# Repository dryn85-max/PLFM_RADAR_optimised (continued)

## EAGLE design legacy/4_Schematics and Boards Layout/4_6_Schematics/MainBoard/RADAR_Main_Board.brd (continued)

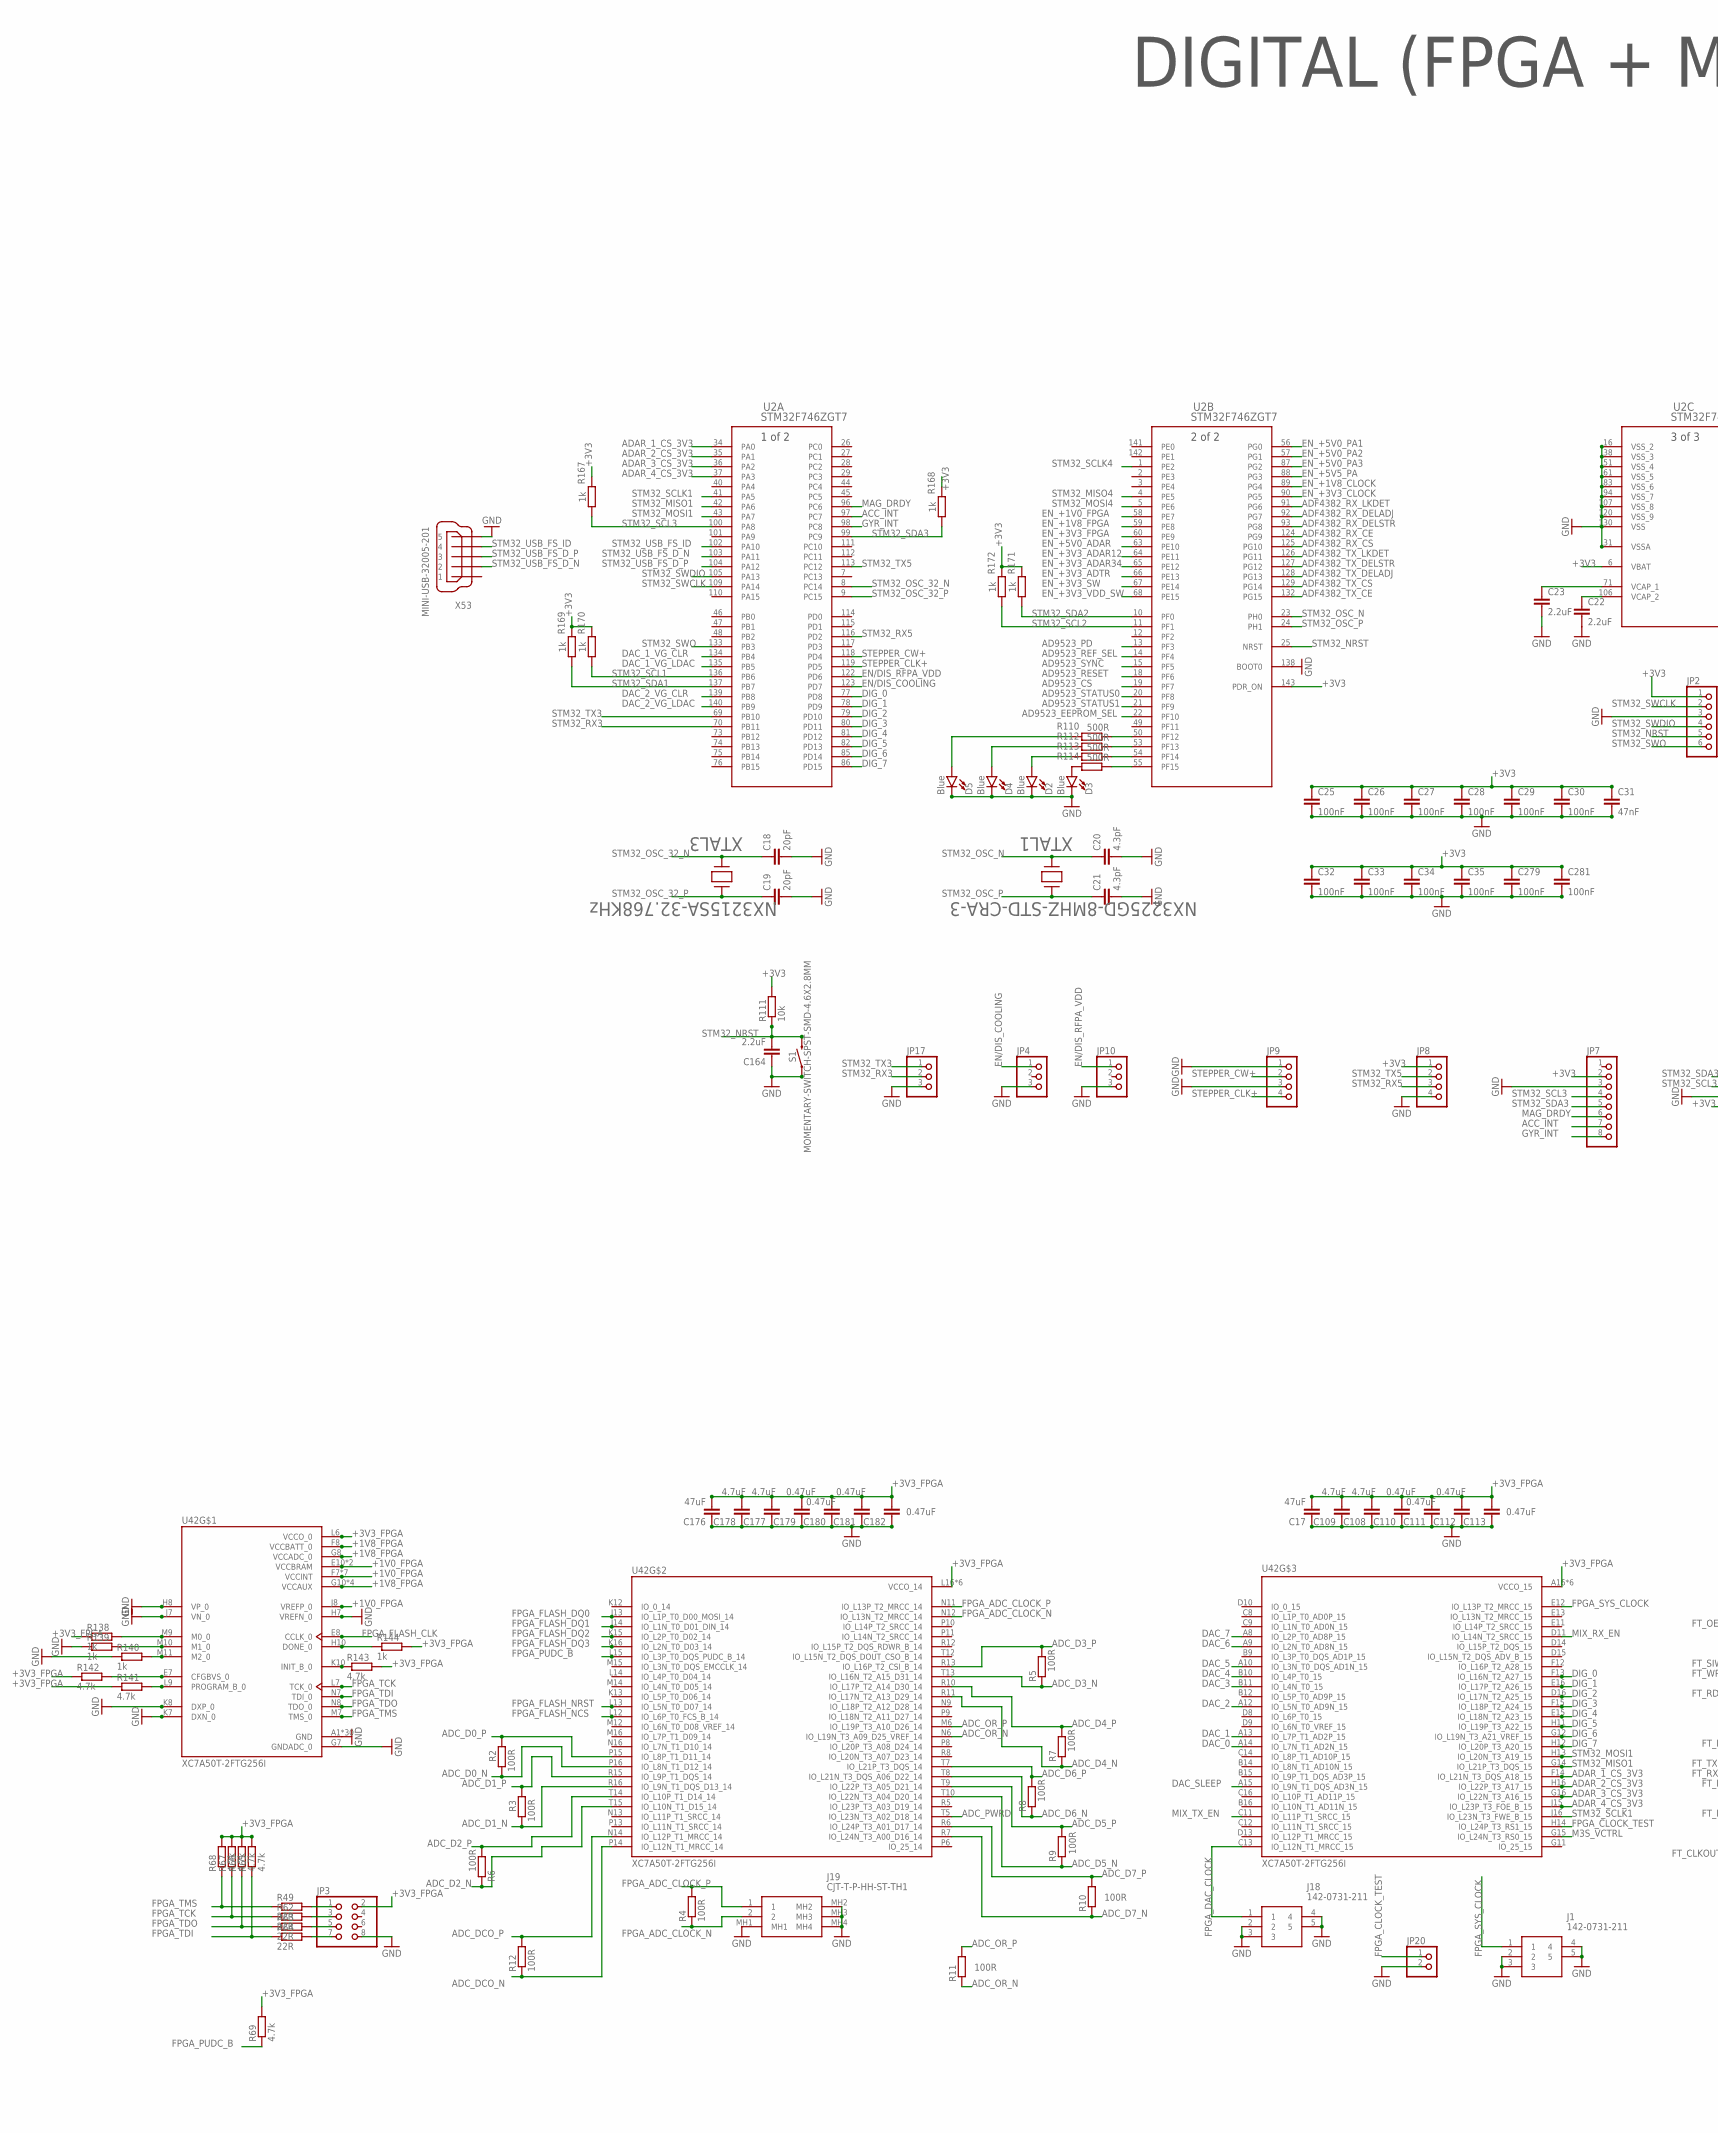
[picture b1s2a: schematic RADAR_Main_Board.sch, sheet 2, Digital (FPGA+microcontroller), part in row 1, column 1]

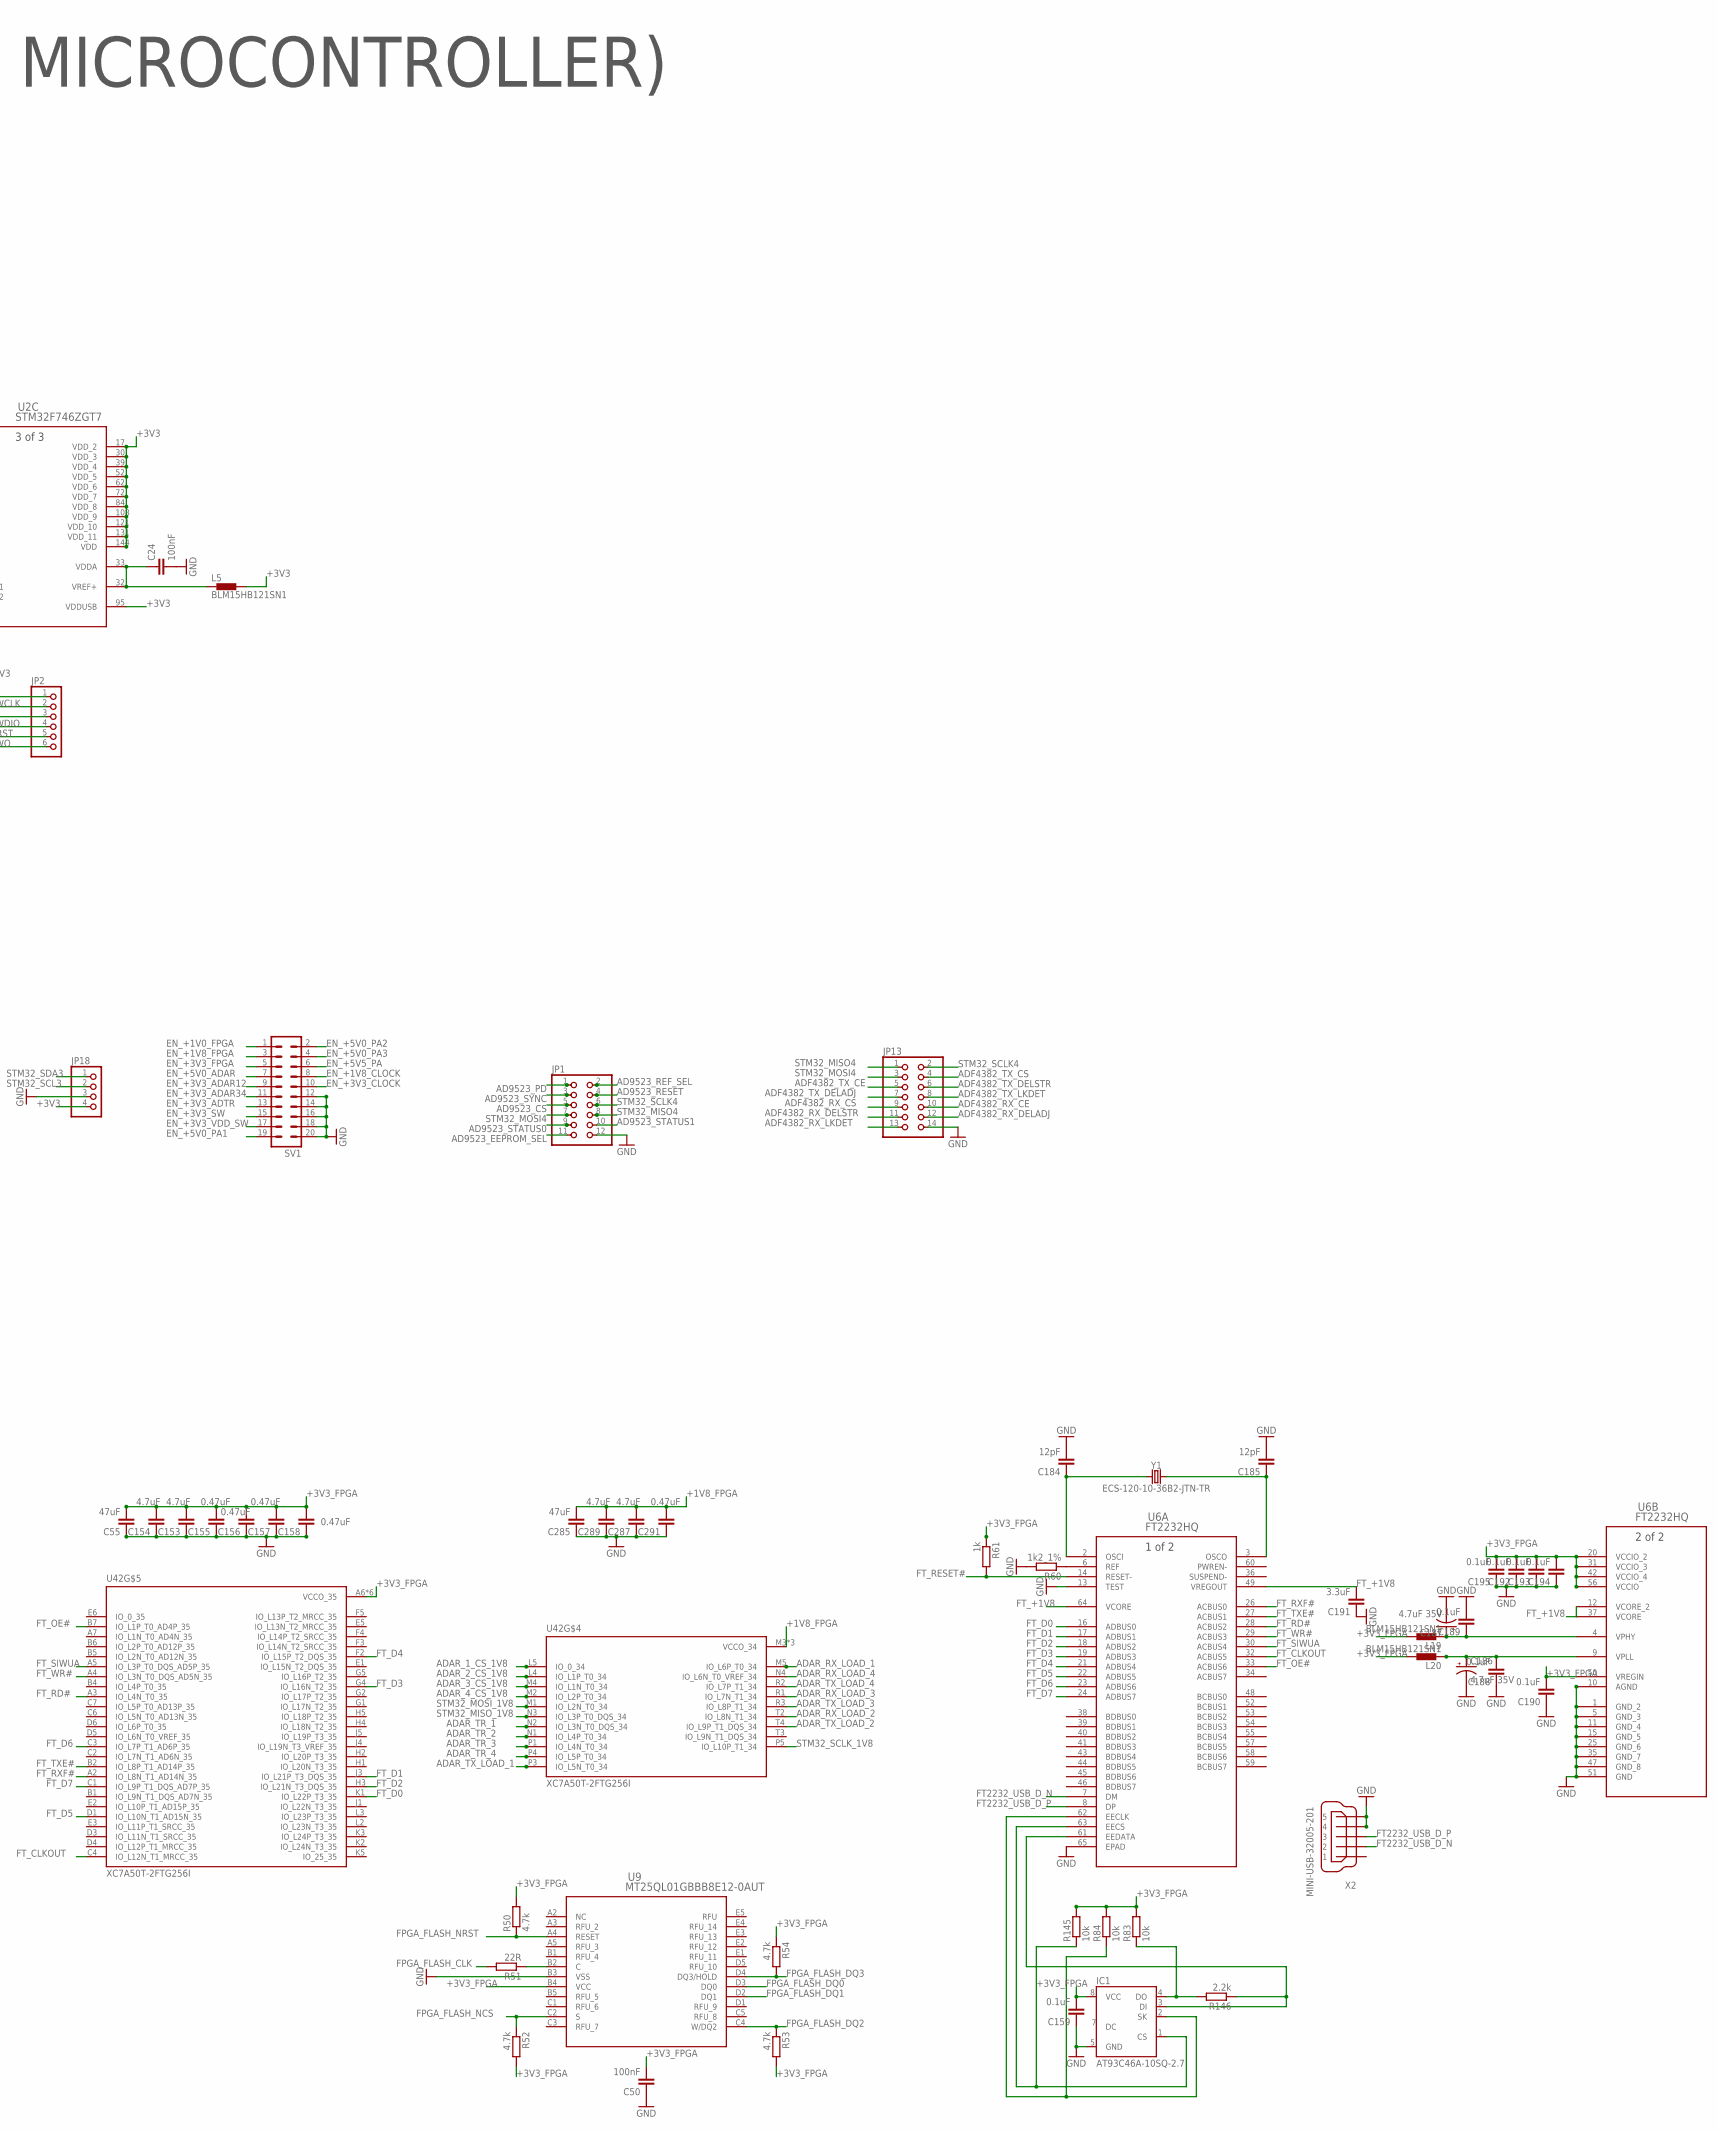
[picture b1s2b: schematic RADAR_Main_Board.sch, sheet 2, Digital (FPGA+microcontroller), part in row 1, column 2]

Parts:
C17, C55, C176, C285: 47uF; C0201
C18, C19: 20pF; C0201
C20, C21: 4.3pF; C0201
C22, C23, C164: 2.2uF; C0201
C24, C25, C26, C27, C28, C29, C30, C32, C33, C34, C35, C50, C279, C281: 100nF; C0201
C31: 47nF; C0201
C108, C109, C153, C154, C177, C178, C287, C289: 4.7uF; C0201
C110, C111, C112, C113, C155, C156, C157, C158, C179, C180, C181, C182, C291: 0.47uF; C0201
C159, C188, C189, C190, C192, C193, C194, C195: 0.1uF; C0201
C184, C185: 12pF; C0201
C186, C187: 4.7uF 35V; EIA3528
C191: 3.3uF; C0201
D2, D3, D4, D5: Blue; LED-0603
IC1: AT93C46A-10SQ-2.7; SOIC8
J1, J18: 142-0731-211; 1420731211
J19: CJT-T-P-HH-ST-TH1; CJTTPHHSTTH1
JP1: PINHD-2X6; 2X06
JP2: PINHD-1X6; 1X06
JP3: PINHD-2X4; 2X04
JP4, JP10, JP17: PINHD-1X3; 1X03
JP7: PINHD-1X8; 1X08
JP8, JP9, JP18: PINHD-1X4; 1X04
JP13: PINHD-2X7; 2X07
JP20: PINHD-1X2; 1X02
L5, L19, L20: BLM15HB121SN1; 0402
R2, R3, R4, R5, R6, R7, R8, R9, R10, R11, R12: 100R; R0201
R49, R51, R62, R63, R64: 22R; R0201
R50, R52, R53, R54, R65, R66, R67, R68, R69, R141, R142, R143: 4.7k; R0201
R60: 1k2_1%; R0201
R61, R138, R139, R140, R144, R167, R168, R169, R170, R171, R172: 1k; R0201
R83, R84, R111, R145: 10k; R0201
R110, R112, R113, R114: 500R; R0201
R146: 2.2k; R0201
S1: MOMENTARY-SWITCH-SPST-SMD-4.6X2.8MM; TACTILE_SWITCH_SMD_4.6X2.8MM
SV1: MA10-2
U2: STM32F746ZGT7; LQFP-144_STM
U6: FT2232HQ; 64QFN_FT2232HQ_FTD
U9: MT25QL01GBBB8E12-0AUT; BGA24_MT25QL_MRN
U42: XC7A50T-2FTG256I; BGA256C100P16X16_1700X1700X155
X2, X53: MINI-USB-32005-201; 32005-201
XTAL1: NX3225GD-8MHZ-STD-CRA-3; XTAL_NX3225GD-8MHZ-STD-CRA-3_N
XTAL3: NX3215SA-32.768KHz; XTAL_NX3225GD-8MHZ-STD-CRA-3_N
Y1: ECS-120-10-36B2-JTN-TR; CRYSTAL-SMD-2X2.5MM

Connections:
+1V0_FPGA: U42.E10 (VCCBRAM), U42.F7 (VCCINT), U42.F9 (VCCINT), U42.F11 (VCCBRAM), U42.G6 (VCCINT), U42.H9 (VCCINT), U42.J6 (VCCINT), U42.J8 (VREFP_0), U42.K9 (VCCINT), U42.L8 (VCCINT); also elsewhere on the board
+1V8_FPGA: C285.2, C287.2, C289.2, C291.2, U42.F8 (VCCBATT_0), U42.G8 (VCCADC_0), U42.G10 (VCCAUX), U42.J10 (VCCAUX), U42.K11 (VCCAUX), U42.L10 (VCCAUX), U42.M3 (VCCO_34), U42.R4 (VCCO_34), U42.T1 (VCCO_34); also elsewhere on the board
+3V3: C25.1, C26.1, C27.1, C28.1, C29.1, C30.1, C31.1, C32.1, C33.1, C34.1, C35.1, C279.1, C281.1, JP2.1, JP7.2, JP8.1, JP18.4, L5.2, R111.2, R167.1, R168.1, R169.1, R170.1, R171.1, R172.1, U2.6 (VBAT), U2.17 (VDD_2), U2.30 (VDD_3), U2.39 (VDD_4), U2.52 (VDD_5), U2.62 (VDD_6), U2.72 (VDD_7), U2.84 (VDD_8), U2.95 (VDDUSB), U2.108 (VDD_9), U2.121 (VDD_10), U2.131 (VDD_11), U2.143 (PDR_ON), U2.144 (VDD); also elsewhere on the board
+3V3_FPGA: C17.2, C50.2, C55.2, C108.2, C109.2, C110.2, C111.2, C112.2, C113.2, C153.2, C154.2, C155.2, C156.2, C157.2, C158.2, C159.2, C176.2, C177.2, C178.2, C179.2, C180.2, C181.2, C182.2, C190.2, C192.2, C193.2, C194.2, C195.2, IC1.8 (VCC), JP3.2, L19.2, L20.2, R50.2, R52.2, R53.2, R54.1, R61.1, R65.2, R66.2, R67.2, R68.2, R69.2, R83.2, R84.2, R138.1, R141.1, R142.1, R143.2, R144.2, R145.2, U6.20 (VCCIO_2), U6.31 (VCCIO_3), U6.42 (VCCIO_4), U6.50 (VREGIN), U6.56 (VCCIO), U9.B4 (VCC), U42.A6 (VCCO_35), U42.A16 (VCCO_15), U42.B3 (VCCO_35), U42.B13 (VCCO_15), U42.C10 (VCCO_15), U42.D7 (VCCO_35), U42.E4 (VCCO_35), U42.E14 (VCCO_15), U42.F1 (VCCO_35), U42.H15 (VCCO_15), U42.J2 (VCCO_35), U42.J12 (VCCO_15), U42.L6 (VCCO_0), U42.L16 (VCCO_14), U42.M13 (VCCO_14), U42.N10 (VCCO_14), U42.P7 (VCCO_14), U42.R14 (VCCO_14), U42.T11 (VCCO_14); also elsewhere on the board
ACC_INT: JP7.7, U2.97 (PC7)
AD9523_CS: JP1.5, U2.19 (PF7)
AD9523_EEPROM_SEL: JP1.11, U2.22 (PF10)
AD9523_PD: JP1.1, U2.13 (PF3)
AD9523_REF_SEL: JP1.2, U2.14 (PF4)
AD9523_RESET: JP1.4, U2.18 (PF6)
AD9523_STATUS0: JP1.9, U2.20 (PF8)
AD9523_STATUS1: JP1.10, U2.21 (PF9)
AD9523_SYNC: JP1.3, U2.15 (PF5)
ADAR_1_CS_1V8: U42.L5 (IO_0_34); also elsewhere on the board
ADAR_1_CS_3V3: U2.34 (PA0), U42.F14 (IO_L21N_T3_DQS_A18_15)
ADAR_2_CS_1V8: U42.L4 (IO_L1P_T0_34); also elsewhere on the board
ADAR_2_CS_3V3: U2.35 (PA1), U42.H16 (IO_L22P_T3_A17_15)
ADAR_3_CS_1V8: U42.M4 (IO_L1N_T0_34); also elsewhere on the board
ADAR_3_CS_3V3: U2.36 (PA2), U42.G16 (IO_L22N_T3_A16_15)
ADAR_4_CS_1V8: U42.M2 (IO_L2P_T0_34); also elsewhere on the board
ADAR_4_CS_3V3: U2.37 (PA3), U42.J15 (IO_L23P_T3_FOE_B_15)
ADAR_RX_LOAD_1: U42.M5 (IO_L6P_T0_34); also elsewhere on the board
ADAR_RX_LOAD_2: U42.T2 (IO_L8N_T1_34); also elsewhere on the board
ADAR_RX_LOAD_3: U42.R1 (IO_L7N_T1_34); also elsewhere on the board
ADAR_RX_LOAD_4: U42.N4 (IO_L6N_T0_VREF_34); also elsewhere on the board
ADAR_TR_1: U42.N2 (IO_L3N_T0_DQS_34); also elsewhere on the board
ADAR_TR_2: U42.N1 (IO_L4P_T0_34); also elsewhere on the board
ADAR_TR_3: U42.P1 (IO_L4N_T0_34); also elsewhere on the board
ADAR_TR_4: U42.P4 (IO_L5P_T0_34); also elsewhere on the board
ADAR_TX_LOAD_1: U42.P3 (IO_L5N_T0_34); also elsewhere on the board
ADAR_TX_LOAD_2: U42.T4 (IO_L9P_T1_DQS_34); also elsewhere on the board
ADAR_TX_LOAD_3: U42.R3 (IO_L8P_T1_34); also elsewhere on the board
ADAR_TX_LOAD_4: U42.R2 (IO_L7P_T1_34); also elsewhere on the board
ADC_D0_N: R2.1, U42.P16 (IO_L8N_T1_D12_14); also elsewhere on the board
ADC_D0_P: R2.2, U42.P15 (IO_L8P_T1_D11_14); also elsewhere on the board
ADC_D1_N: R3.1, U42.R16 (IO_L9N_T1_DQS_D13_14); also elsewhere on the board
ADC_D1_P: R3.2, U42.R15 (IO_L9P_T1_DQS_14); also elsewhere on the board
ADC_D2_N: R6.1, U42.T15 (IO_L10N_T1_D15_14); also elsewhere on the board
ADC_D2_P: R6.2, U42.T14 (IO_L10P_T1_D14_14); also elsewhere on the board
ADC_D3_N: R5.1, U42.T13 (IO_L16N_T2_A15_D31_14); also elsewhere on the board
ADC_D3_P: R5.2, U42.R13 (IO_L16P_T2_CSI_B_14); also elsewhere on the board
ADC_D4_N: R7.1, U42.R11 (IO_L17N_T2_A13_D29_14); also elsewhere on the board
ADC_D4_P: R7.2, U42.R10 (IO_L17P_T2_A14_D30_14); also elsewhere on the board
ADC_D5_N: R9.1, U42.T10 (IO_L22N_T3_A04_D20_14); also elsewhere on the board
ADC_D5_P: R9.2, U42.T9 (IO_L22P_T3_A05_D21_14); also elsewhere on the board
ADC_D6_N: R8.1, U42.T8 (IO_L21N_T3_DQS_A06_D22_14); also elsewhere on the board
ADC_D6_P: R8.2, U42.T7 (IO_L21P_T3_DQS_14); also elsewhere on the board
ADC_D7_N: R10.1, U42.R7 (IO_L24N_T3_A00_D16_14); also elsewhere on the board
ADC_D7_P: R10.2, U42.R6 (IO_L24P_T3_A01_D17_14); also elsewhere on the board
ADC_DCO_N: R12.1, U42.P14 (IO_L12N_T1_MRCC_14); also elsewhere on the board
ADC_DCO_P: R12.2, U42.N14 (IO_L12P_T1_MRCC_14); also elsewhere on the board
ADC_OR_N: R11.1, U42.N6 (IO_L19N_T3_A09_D25_VREF_14); also elsewhere on the board
ADC_OR_P: R11.2, U42.M6 (IO_L19P_T3_A10_D26_14); also elsewhere on the board
ADC_PWRD: U42.T5 (IO_L23N_T3_A02_D18_14); also elsewhere on the board
ADF4382_RX_CE: JP13.10, U2.124 (PG9)
ADF4382_RX_CS: JP13.9, U2.125 (PG10)
ADF4382_RX_DELADJ: JP13.12, U2.92 (PG7)
ADF4382_RX_DELSTR: JP13.11, U2.93 (PG8)
ADF4382_RX_LKDET: JP13.13, U2.91 (PG6)
ADF4382_TX_CE: JP13.5, U2.132 (PG15)
ADF4382_TX_CS: JP13.4, U2.129 (PG14)
ADF4382_TX_DELADJ: JP13.7, U2.128 (PG13)
ADF4382_TX_DELSTR: JP13.6, U2.127 (PG12)
ADF4382_TX_LKDET: JP13.8, U2.126 (PG11)
DAC_0: U42.A14 (IO_L7N_T1_AD2N_15); also elsewhere on the board
DAC_1: U42.A13 (IO_L7P_T1_AD2P_15); also elsewhere on the board
DAC_1_VG_CLR: U2.134 (PB4); also elsewhere on the board
DAC_1_VG_LDAC: U2.135 (PB5); also elsewhere on the board
DAC_2: U42.A12 (IO_L5N_T0_AD9N_15); also elsewhere on the board
DAC_2_VG_CLR: U2.139 (PB8); also elsewhere on the board
DAC_2_VG_LDAC: U2.140 (PB9); also elsewhere on the board
DAC_3: U42.B11 (IO_L4N_T0_15); also elsewhere on the board
DAC_4: U42.B10 (IO_L4P_T0_15); also elsewhere on the board
DAC_5: U42.A10 (IO_L3N_T0_DQS_AD1N_15); also elsewhere on the board
DAC_6: U42.A9 (IO_L2N_T0_AD8N_15); also elsewhere on the board
DAC_7: U42.A8 (IO_L2P_T0_AD8P_15); also elsewhere on the board
DAC_SLEEP: U42.A15 (IO_L9N_T1_DQS_AD3N_15); also elsewhere on the board
DIG_0: U2.77 (PD8), U42.F13 (IO_L16N_T2_A27_15)
DIG_1: U2.78 (PD9), U42.E16 (IO_L17P_T2_A26_15)
DIG_2: U2.79 (PD10), U42.D16 (IO_L17N_T2_A25_15)
DIG_3: U2.80 (PD11), U42.F15 (IO_L18P_T2_A24_15)
DIG_4: U2.81 (PD12), U42.E15 (IO_L18N_T2_A23_15)
DIG_5: U2.82 (PD13), U42.H11 (IO_L19P_T3_A22_15)
DIG_6: U2.85 (PD14), U42.G12 (IO_L19N_T3_A21_VREF_15)
DIG_7: U2.86 (PD15), U42.H12 (IO_L20P_T3_A20_15)
EN/DIS_COOLING: JP4.1, U2.123 (PD7)
EN/DIS_RFPA_VDD: JP10.1, U2.122 (PD6)
EN_+1V0_FPGA: SV1.1, U2.58 (PE7)
EN_+1V8_CLOCK: SV1.8, U2.89 (PG4)
EN_+1V8_FPGA: SV1.3, U2.59 (PE8)
EN_+3V3_ADAR12: SV1.9, U2.64 (PE11)
EN_+3V3_ADAR34: SV1.11, U2.65 (PE12)
EN_+3V3_ADTR: SV1.13, U2.66 (PE13)
EN_+3V3_CLOCK: SV1.10, U2.90 (PG5)
EN_+3V3_FPGA: SV1.5, U2.60 (PE9)
EN_+3V3_SW: SV1.15, U2.67 (PE14)
EN_+3V3_VDD_SW: SV1.17, U2.68 (PE15)
EN_+5V0_ADAR: SV1.7, U2.63 (PE10)
EN_+5V0_PA1: SV1.19, U2.56 (PG0)
EN_+5V0_PA2: SV1.2, U2.57 (PG1)
EN_+5V0_PA3: SV1.4, U2.87 (PG2)
EN_+5V5_PA: SV1.6, U2.88 (PG3)
FPGA_ADC_CLOCK_N: J19.2, R4.1, U42.N12 (IO_L13N_T2_MRCC_14)
FPGA_ADC_CLOCK_P: J19.1, R4.2, U42.N11 (IO_L13P_T2_MRCC_14)
FPGA_CLOCK_TEST: JP20.1, U42.H14 (IO_L24P_T3_RS1_15)
FPGA_DAC_CLOCK: J18.1, U42.C13 (IO_L12N_T1_MRCC_15)
FPGA_FLASH_CLK: R51.2, U42.E8 (CCLK_0)
FPGA_FLASH_DQ0: U9.D3 (DQ0), U42.J13 (IO_L1P_T0_D00_MOSI_14)
FPGA_FLASH_DQ1: U9.D2 (DQ1), U42.J14 (IO_L1N_T0_D01_DIN_14)
FPGA_FLASH_DQ2: R53.1, U9.C4 (W/DQ2), U42.K15 (IO_L2P_T0_D02_14)
FPGA_FLASH_DQ3: R54.2, U9.D4 (DQ3/HOLD), U42.K16 (IO_L2N_T0_D03_14)
FPGA_FLASH_NCS: R52.1, U9.C2 (S), U42.L12 (IO_L6P_T0_FCS_B_14)
FPGA_FLASH_NRST: R50.1, U9.A4 (RESET), U42.L13 (IO_L5N_T0_D07_14)
FPGA_PUDC_B: R69.1, U42.L15 (IO_L3P_T0_DQS_PUDC_B_14)
FPGA_SYS_CLOCK: J1.1, U42.E12 (IO_L13P_T2_MRCC_15)
FPGA_TCK: R62.1, R67.1, U42.L7 (TCK_0)
FPGA_TDI: R64.1, R65.1, U42.N7 (TDI_0)
FPGA_TDO: R63.1, R66.1, U42.N8 (TDO_0)
FPGA_TMS: R49.1, R68.1, U42.M7 (TMS_0)
FT2232_USB_D_N: U6.7 (DM), X2.2
FT2232_USB_D_P: U6.8 (DP), X2.3
FT_+1V8: C191.2, U6.12 (VCORE_2), U6.37 (VCORE), U6.49 (VREGOUT), U6.64 (VCORE)
FT_CLKOUT: U6.32 (ACBUS5), U42.C4 (IO_L12N_T1_MRCC_35)
FT_D0: U6.16 (ADBUS0), U42.K1 (IO_L22P_T3_35)
FT_D1: U6.17 (ADBUS1), U42.J3 (IO_L21P_T3_DQS_35)
FT_D2: U6.18 (ADBUS2), U42.H3 (IO_L21N_T3_DQS_35)
FT_D3: U6.19 (ADBUS3), U42.G4 (IO_L16N_T2_35)
FT_D4: U6.21 (ADBUS4), U42.F2 (IO_L15P_T2_DQS_35)
FT_D5: U6.22 (ADBUS5), U42.D1 (IO_L10N_T1_AD15N_35)
FT_D6: U6.23 (ADBUS6), U42.C3 (IO_L7P_T1_AD6P_35)
FT_D7: U6.24 (ADBUS7), U42.C1 (IO_L9P_T1_DQS_AD7P_35)
FT_OE#: U6.33 (ACBUS6), U42.B7 (IO_L1P_T0_AD4P_35)
FT_RD#: U6.28 (ACBUS2), U42.A3 (IO_L4N_T0_35)
FT_RESET#: R61.2, U6.14 (RESET-)
FT_RXF#: U6.26 (ACBUS0), U42.A2 (IO_L8N_T1_AD14N_35)
FT_SIWUA: U6.30 (ACBUS4), U42.A5 (IO_L3P_T0_DQS_AD5P_35)
FT_TXE#: U6.27 (ACBUS1), U42.B2 (IO_L8P_T1_AD14P_35)
FT_WR#: U6.29 (ACBUS3), U42.A4 (IO_L3N_T0_DQS_AD5N_35)
GND: C17.1, C18.2, C19.2, C20.2, C21.2, C22.2, C23.2, C24.2, C25.2, C26.2, C27.2, C28.2, C29.2, C30.2, C31.2, C32.2, C33.2, C34.2, C35.2, C50.1, C55.1, C108.1, C109.1, C110.1, C111.1, C112.1, C113.1, C153.1, C154.1, C155.1, C156.1, C157.1, C158.1, C159.1, C164.1, C176.1, C177.1, C178.1, C179.1, C180.1, C181.1, C182.1, C184.2, C185.2, C186.C (-), C187.C (-), C188.1, C189.2, C190.1, C191.1, C192.1, C193.1, C194.1, C195.1, C279.2, C281.2, C285.1, C287.1, C289.1, C291.1, D2.C, D3.C, D4.C, D5.C, IC1.5 (GND), J1.2, J1.3, J1.4, J1.5, J18.2, J18.3, J18.4, J18.5, J19.MH1, J19.MH2, J19.MH3, J19.MH4, JP1.12, JP2.3, JP3.8, JP4.3, JP7.3, JP8.4, JP9.1, JP9.3, JP10.3, JP13.14, JP17.3, JP18.3, JP20.2, R60.2, R139.1, R140.1, S1.1, S1.2 (1), SV1.12, SV1.14, SV1.16, SV1.18, SV1.20, U2.16 (VSS_2), U2.31 (VSSA), U2.38 (VSS_3), U2.51 (VSS_4), U2.61 (VSS_5), U2.83 (VSS_6), U2.94 (VSS_7), U2.107 (VSS_8), U2.120 (VSS_9), U2.130 (VSS), U2.138 (BOOT0), U6.1 (GND_2), U6.5 (GND_3), U6.10 (AGND), U6.11 (GND_4), U6.13 (TEST), U6.15 (GND_5), U6.25 (GND_6), U6.35 (GND_7), U6.47 (GND_8), U6.51 (GND), U6.65 (EPAD), U9.B3 (VSS), U42.A1 (GND), U42.A11 (GND), U42.B8 (GND), U42.C5 (GND), U42.C15 (GND), U42.D2 (GND), U42.D12 (GND), U42.E9 (GND), U42.F6 (GND), U42.F10 (GND), U42.F16 (GND), U42.G3 (GND), U42.G7 (GNDADC_0), U42.G9 (GND), U42.G13 (GND), U42.H6 (GND), U42.H7 (VREFN_0), U42.H8 (VP_0), U42.J7 (VN_0), U42.J9 (GND), U42.J11 (GND), U42.K4 (GND), U42.K6 (GND), U42.K7 (DXN_0), U42.K8 (DXP_0), U42.K14 (GND), U42.L1 (GND), U42.L11 (GND), U42.M8 (GND), U42.N5 (GND), U42.N15 (GND), U42.P2 (GND), U42.P12 (GND), U42.R9 (GND), U42.T6 (GND), U42.T16 (GND), X2.4, X2.5, X53.5; also elsewhere on the board
GYR_INT: JP7.8, U2.98 (PC8)
M3S_VCTRL: U42.G15 (IO_L24N_T3_RS0_15); also elsewhere on the board
MAG_DRDY: JP7.6, U2.96 (PC6)
MIX_RX_EN: U42.D11 (IO_L14N_T2_SRCC_15); also elsewhere on the board
MIX_TX_EN: U42.C11 (IO_L11P_T1_SRCC_15); also elsewhere on the board
unnamed: C23.1, U2.71 (VCAP_1)
unnamed: C22.1, U2.106 (VCAP_2)
unnamed: C24.1, L5.1, U2.32 (VREF+), U2.33 (VDDA)
unnamed: R51.1, U9.B2 (C)
unnamed: JP3.1, R49.2
unnamed: JP3.3, R62.2
unnamed: JP3.5, R63.2
unnamed: JP3.7, R64.2
unnamed: R110.2, U2.50 (PF12)
unnamed: IC1.4 (DO), R83.1, R146.2
unnamed: R112.2, U2.53 (PF13)
unnamed: D3.A, R114.1
unnamed: R113.2, U2.54 (PF14)
unnamed: R114.2, U2.55 (PF15)
unnamed: D2.A, R113.1
unnamed: D4.A, R112.1
unnamed: D5.A, R110.1
unnamed: R138.2, U42.M9 (M0_0)
unnamed: R139.2, U42.M10 (M1_0)
unnamed: R140.2, U42.M11 (M2_0)
unnamed: R141.2, U42.L9 (PROGRAM_B_0)
unnamed: R142.2, U42.E7 (CFGBVS_0)
unnamed: R144.1, U42.H10 (DONE_0)
unnamed: R143.1, U42.K10 (INIT_B_0)
unnamed: R60.1, U6.6 (REF)
unnamed: C184.1, U6.2 (OSCI), Y1.P1 (1)
unnamed: C185.1, U6.3 (OSCO), Y1.P3 (2)
unnamed: C186.A (+), C188.2, L20.1, U6.9 (VPLL)
unnamed: C187.A (+), C189.1, L19.1, U6.4 (VPHY)
unnamed: IC1.1 (CS), R145.1, U6.63 (EECS)
unnamed: IC1.2 (SK), R84.1, U6.62 (EECLK)
unnamed: IC1.3 (DI), R146.1, U6.61 (EEDATA)
STEPPER_CLK+: JP9.4, U2.119 (PD5)
STEPPER_CW+: JP9.2, U2.118 (PD4)
STM32_MISO1: U2.42 (PA6), U42.G14 (IO_L21P_T3_DQS_15)
STM32_MISO4: JP1.8, JP13.1, U2.4 (PE5)
STM32_MISO_1V8: U42.N3 (IO_L3P_T0_DQS_34); also elsewhere on the board
STM32_MOSI1: U2.43 (PA7), U42.H13 (IO_L20N_T3_A19_15)
STM32_MOSI4: JP1.7, JP13.3, U2.5 (PE6)
STM32_MOSI_1V8: U42.M1 (IO_L2N_T0_34); also elsewhere on the board
STM32_NRST: C164.2, JP2.5, R111.1, S1.3 (2), S1.4 (2), U2.25 (NRST)
STM32_OSC_32_N: C18.1, U2.8 (PC14), XTAL3.2
STM32_OSC_32_P: C19.1, U2.9 (PC15), XTAL3.1
STM32_OSC_N: C20.1, U2.23 (PH0), XTAL1.2
STM32_OSC_P: C21.1, U2.24 (PH1), XTAL1.1
STM32_RX3: JP17.2, U2.70 (PB11)
STM32_RX5: JP8.3, U2.116 (PD2)
STM32_SCL1: R170.2, U2.136 (PB6); also elsewhere on the board
STM32_SCL2: R172.2, U2.11 (PF1); also elsewhere on the board
STM32_SCL3: JP7.4, JP18.2, R167.2, U2.100 (PA8)
STM32_SCLK1: U2.41 (PA5), U42.J16 (IO_L23N_T3_FWE_B_15)
STM32_SCLK4: JP1.6, JP13.2, U2.1 (PE2)
STM32_SCLK_1V8: U42.P5 (IO_L10P_T1_34); also elsewhere on the board
STM32_SDA1: R169.2, U2.137 (PB7); also elsewhere on the board
STM32_SDA2: R171.2, U2.10 (PF0); also elsewhere on the board
STM32_SDA3: JP7.5, JP18.1, R168.2, U2.99 (PC9)
STM32_SWCLK: JP2.2, U2.109 (PA14)
STM32_SWDIO: JP2.4, U2.105 (PA13)
STM32_SWO: JP2.6, U2.133 (PB3)
STM32_TX3: JP17.1, U2.69 (PB10)
STM32_TX5: JP8.2, U2.113 (PC12)
STM32_USB_FS_D_N: U2.103 (PA11), X53.2
STM32_USB_FS_D_P: U2.104 (PA12), X53.3
STM32_USB_FS_ID: U2.102 (PA10), X53.4

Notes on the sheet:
DIGITAL (FPGA + MICROCONTROLLER)
